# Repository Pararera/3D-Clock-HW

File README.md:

# 3D SEGMENT CLOCK - HARDWARE

<a href="https://github.com/Pararera/3D-Clock-SW" title="Repo for software development." target="_blank">Software repo</a>
<br/>
<a href="#" title="Arduino Project Hub page" target="_blank">Link to the project page (soon)</a>

The project is in WIP stage. New stuff soon.

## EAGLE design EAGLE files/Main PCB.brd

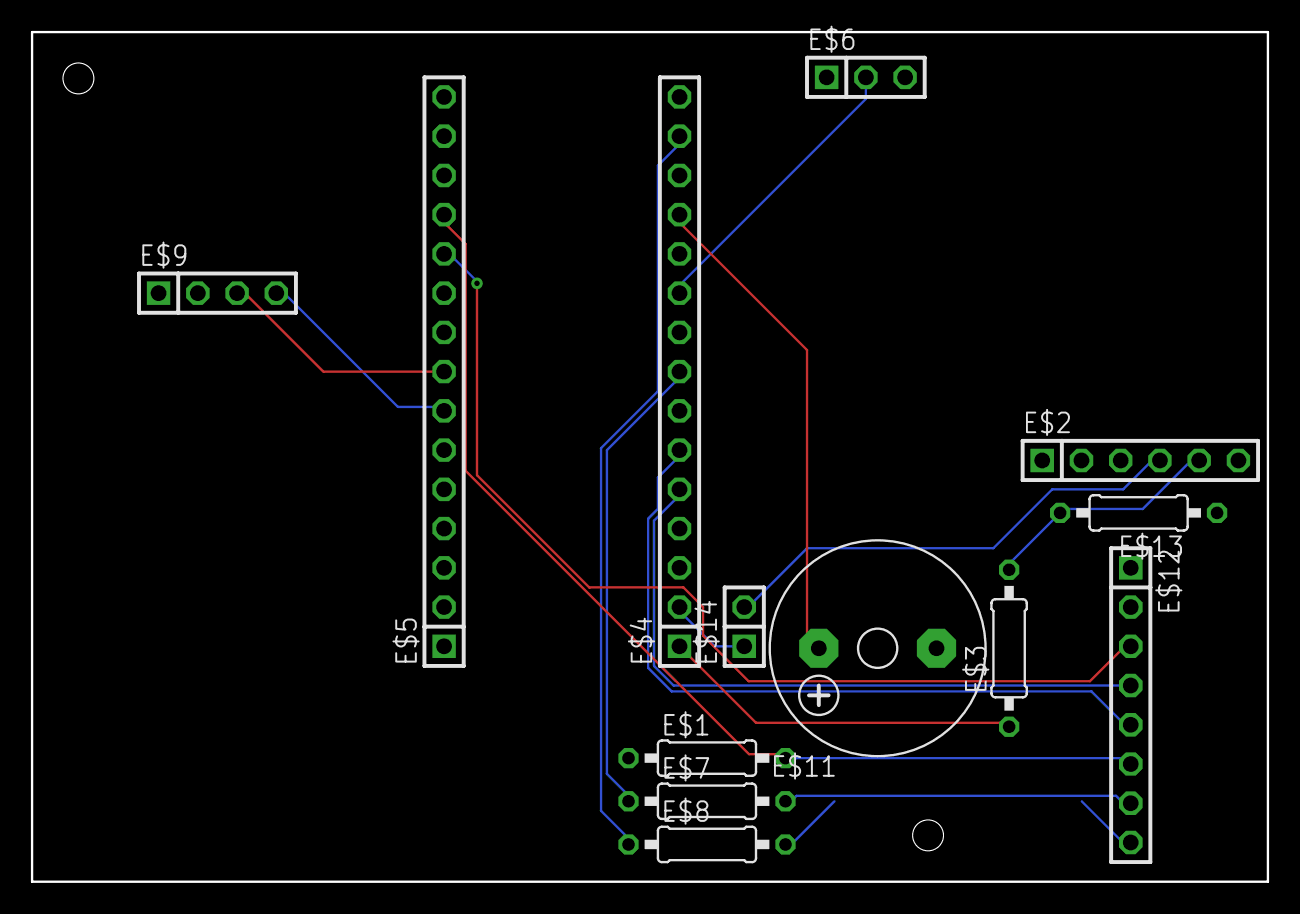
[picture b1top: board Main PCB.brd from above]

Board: 2 copper layers, 80.0 x 55.0 mm, 13 parts (0 on the bottom side), 18 nets.

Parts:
E$1, E$3, E$7, E$8, E$13: 0207/10
E$2: 1X06
E$4, E$5: 1X15
E$6: 1X03
E$9: 1X04
E$11: F/CM12P
E$12: 1X08
E$14: 1X02

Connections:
GND: E$1.1, E$2.3, E$4.4, E$5.2, E$6.1, E$9.1, E$11.-, E$12.1, E$13.1
S$1: E$8.2, E$12.8
S$3: E$4.14, E$8.1
S$4: E$7.2, E$12.7
S$5: E$4.8, E$7.1
S$6: E$1.2, E$5.12, E$12.6
S$8: E$4.5, E$12.4
S$9: E$4.6, E$12.5
S$10: E$4.2, E$14.1
S$11: E$3.1, E$4.1
S$12: E$4.12, E$11.+
S$13: E$4.10, E$6.2
S$14: E$5.11, E$12.3
S$15: E$5.8, E$9.3
S$16: E$5.7, E$9.4
S$17: E$2.5, E$3.2, E$13.2
S$18: E$2.4, E$14.2
VCC: E$2.2, E$5.4, E$6.3, E$9.2, E$12.2

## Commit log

2020-07-04 First commit.
